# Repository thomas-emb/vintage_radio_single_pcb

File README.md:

# Vintage Radio &ndash; Single PCB

This is a single PCB solution to [Zion Brock](https://www.zionbrock.com/radio)'s Vintage Radio project.

---

## 📌 Overview

This repository contains the design files, created using KiCad.
The project includes schematics, PCB layout, and manufacturing outputs.

---

## 🛠️ Design Tools

- EDA Software: KiCad 8.0
- Board Type: **Single** layer whatever-suits-your-needs-material
- Dimensions: 4.85&times;7cm

---

## 📁 Repository Structure

    .
    ├── fabrication/            # Gerbers, drill files, bill-of-materials
    ├── images/                 # Images
    ├── VintageRadio.kicad_pcb  # KiCad PCB layout
    ├── VintageRadio.kicad_pro  # KiCad project
    ├── VintageRadio.kicad_sch  # KiCad schematic
    ├── CHANGELOG.txt
    ├── LICENSE
    └── README.md

---

## 🧩 Components

- RP2040-Zero
- DFPlayer Mini
- Amplifier
- Some resistors, caps, and headers

See the BOM in the [fabrication/]() folder for full details.

---

## 🏭 Fabrication Notes

- Trace widths: 0.4mm
- Drill sizes: 0.8mm (components), 1mm (headers), 2mm (mounting holes)
- Assembly: Hand assembly, check the [YouTube](https://www.youtube.com/watch?v=w2aT9UKJ8m4) video as well.

---

## 📷 Images

Schematic: 
PCB: 

---

## 📄 License

This project is under CC0-1.0 licence, see the [LICENSE]() file for details.

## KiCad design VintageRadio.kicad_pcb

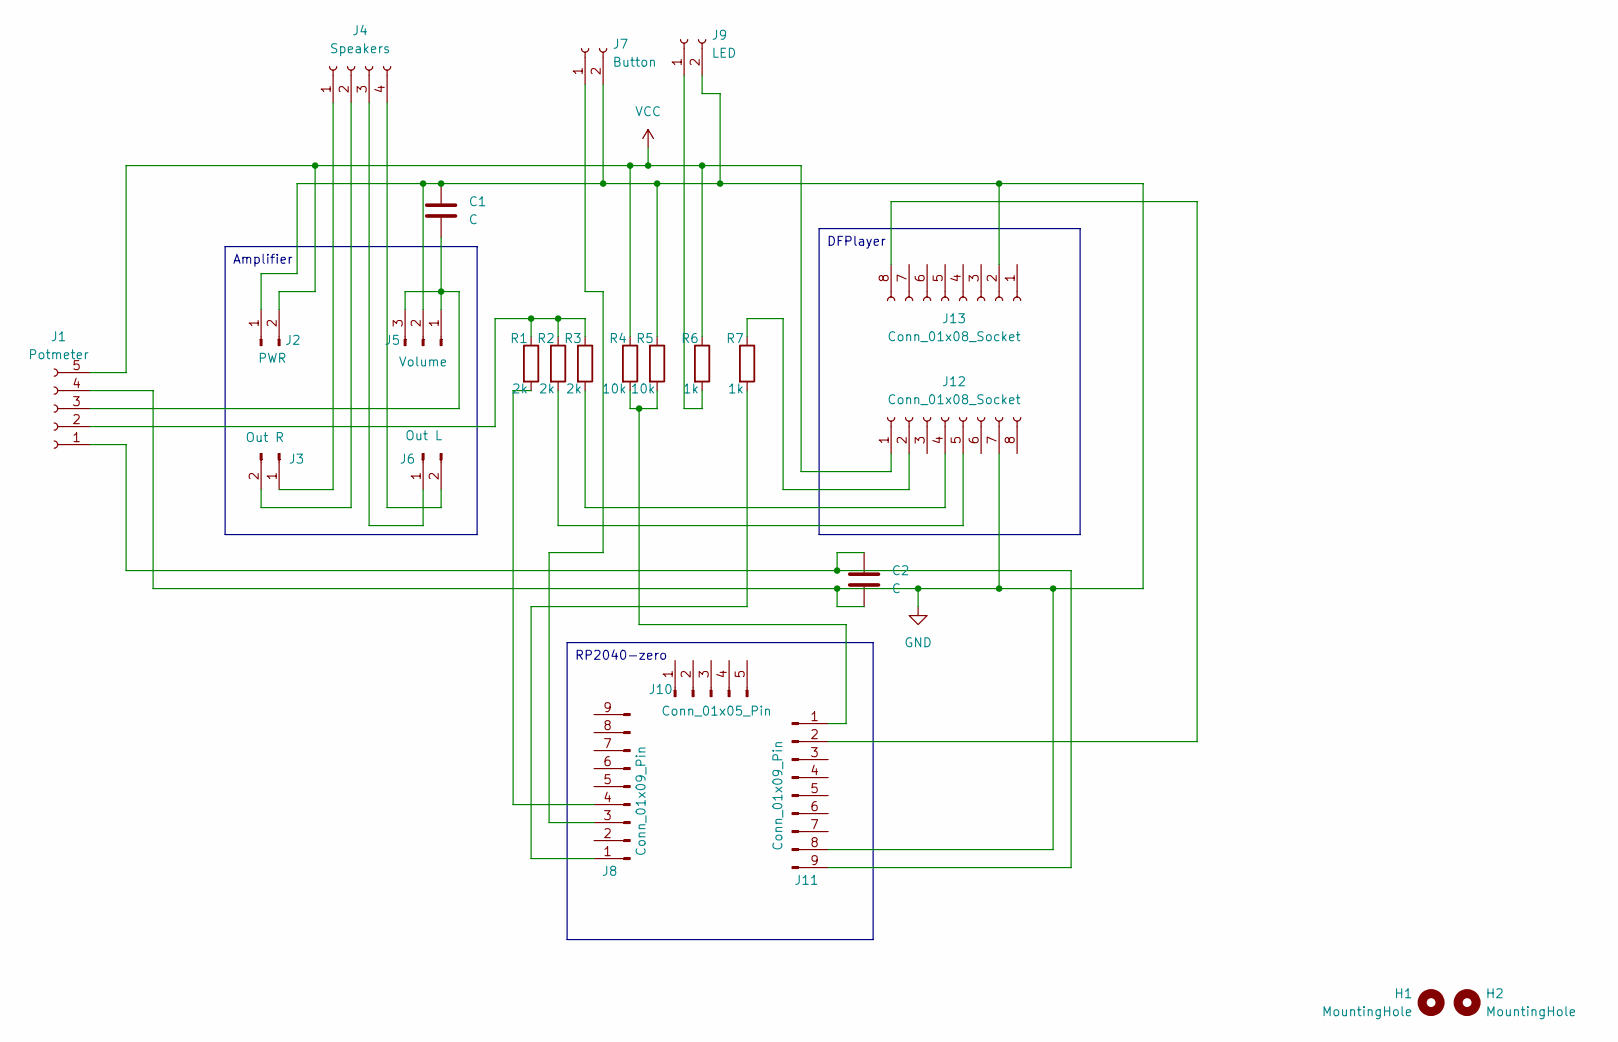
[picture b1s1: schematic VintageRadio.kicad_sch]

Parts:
C1, C2: C; C_Disc_D3.0mm_W1.6mm_P2.50mm
H1, H2: MountingHole; MountingHole_2mm
J1: Potmeter; PinSocket_1x05_P2.54mm_Vertical
J2: PWR; PinHeader_1x02_P2.54mm_Vertical
J3: Out R; PinHeader_1x02_P2.54mm_Vertical
J4: Speakers; PinSocket_1x04_P2.54mm_Vertical
J5: Volume; PinHeader_1x03_P2.54mm_Vertical
J6: Out L; PinHeader_1x02_P2.54mm_Vertical
J7: Button; PinSocket_1x02_P2.54mm_Vertical
J8, J11: Conn_01x09_Pin; PinHeader_1x09_P2.54mm_Vertical
J9: LED; PinSocket_1x02_P2.54mm_Vertical
J10: Conn_01x05_Pin; PinHeader_1x05_P2.54mm_Vertical
J12, J13: Conn_01x08_Socket; PinSocket_1x08_P2.54mm_Vertical
R1, R2, R3: 2k; R_Axial_DIN0207_L6.3mm_D2.5mm_P10.16mm_Horizontal
R4, R5: 10k; R_Axial_DIN0207_L6.3mm_D2.5mm_P10.16mm_Horizontal
R6, R7: 1k; R_Axial_DIN0207_L6.3mm_D2.5mm_P10.16mm_Horizontal

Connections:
GND: C1.2, C2.2, J1.4, J2.1, J5.2, J7.2, J9.2, J11.8, J12.7, J13.2, R5.1
unnamed: C2.1, J1.1, J11.9
unnamed: J1.2, R1.1, R2.1, R3.1
unnamed: C1.1, J1.3, J5.1, J5.3
unnamed: J3.1, J4.1
unnamed: J3.2, J4.2
unnamed: J4.3, J6.1
unnamed: J4.4, J6.2
unnamed: J7.1, J8.3
unnamed: J8.1, R7.2
unnamed: J8.4, R1.2
unnamed: J9.1, R6.2
unnamed: J11.1, R4.2, R5.2
unnamed: J11.2, J13.8
unnamed: J12.2, R7.1
unnamed: J12.4, R3.2
unnamed: J12.5, R2.2
VCC: J1.5, J2.2, J12.1, R4.1, R6.1

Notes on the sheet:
Amplifier
DFPlayer
RP2040-zero

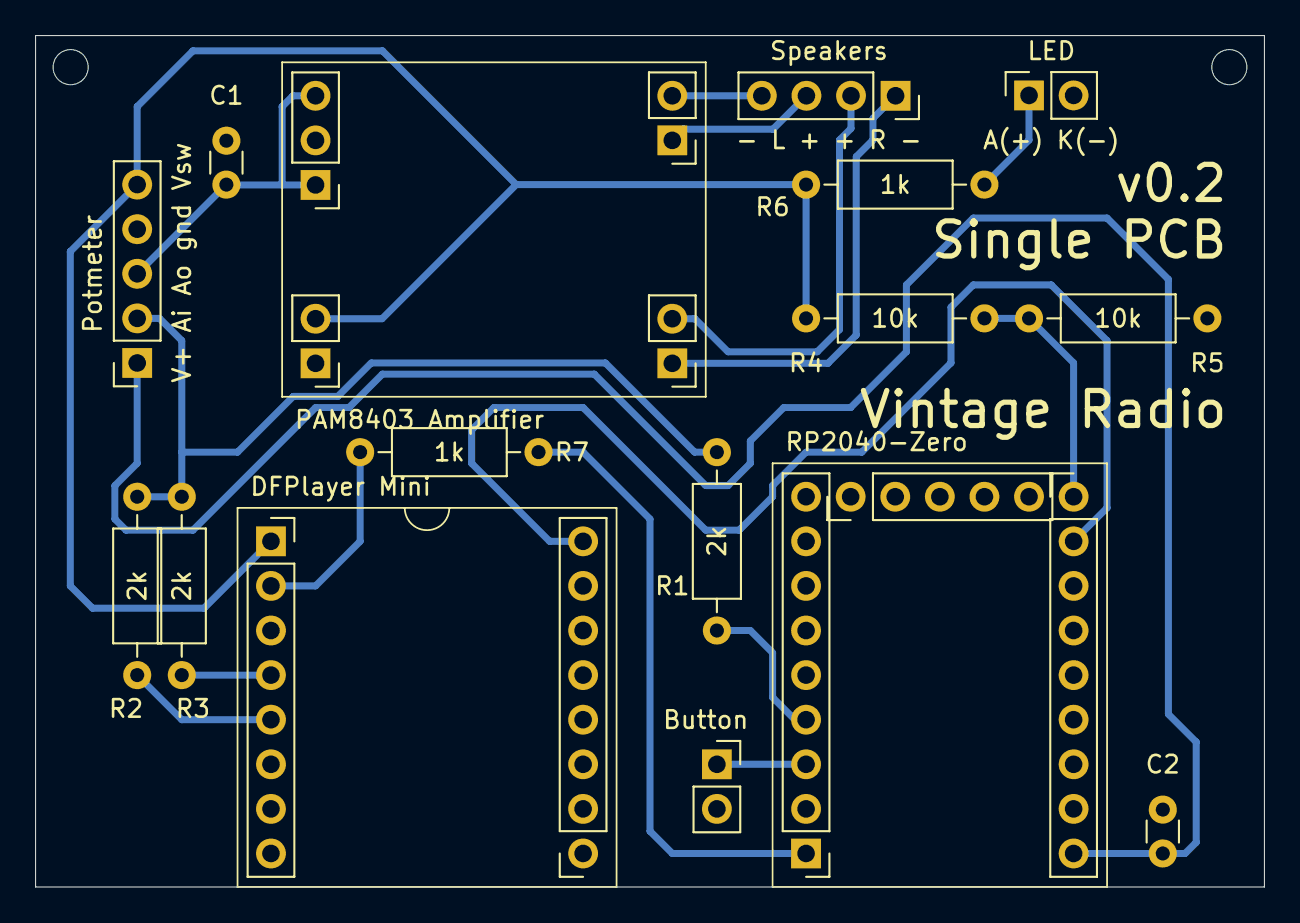
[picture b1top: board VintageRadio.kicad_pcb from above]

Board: 2 copper layers, 70.0 x 48.5 mm, 24 parts (0 on the bottom side), 18 nets.

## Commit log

2026-01-08 v0.1 initial commit
2026-01-09 better component placement
